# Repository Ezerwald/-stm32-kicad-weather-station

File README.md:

# STM32 KiCad Weather Station

KiCad-based PCB project for an STM32-powered IoT weather station with environmental sensing, real-time clock support, battery charging, and e-paper display connectivity.

> 3D render:

## Overview

This project is a custom two-layer PCB designed in KiCad for a compact embedded weather station.  
The board is built around the **STM32F103C8T6** microcontroller and integrates power management, sensing, display, and timekeeping components into a single design.

The main goal of the project was to practice the complete PCB design workflow: schematic capture, component selection, board layout, and preparation of production files.

## Main features

- STM32F103C8T6 microcontroller
- BME280 environmental sensor
- DS3231S real-time clock
- E-paper display connector
- TP4056 Li-ion battery charging circuit
- AMS1117-3.3 voltage regulator
- USB-C power input
- 5 control buttons
- Status LEDs

## Hardware components

### Core components
- **U1** — STM32F103C8T6
- **U2** — BME280
- **U3** — TP4056
- **U4** — AMS1117-3.3
- **U5** — DS3231S

### Connectors and interfaces
- **P1** — USB_C_Plug
- **J1** — Battery
- **J2** — Prog
- **J3** — E-Paper_Display

### User interface
- **SW1–SW5** — buttons
- **D1** — Blue LED
- **D2** — Green LED
- **D3** — Red LED

## Design files

> Schematic:

> PCB layout:

## Notes

This repository focuses mainly on the PCB design itself rather than firmware implementation.  
The project includes the main design files, screenshots, and fabrication outputs for documentation purposes.

## Tools used

- **KiCad** for schematic and PCB design
- Optional 3D viewer/export from KiCad for board rendering

## Author

**Vladyslav Kyshchun**

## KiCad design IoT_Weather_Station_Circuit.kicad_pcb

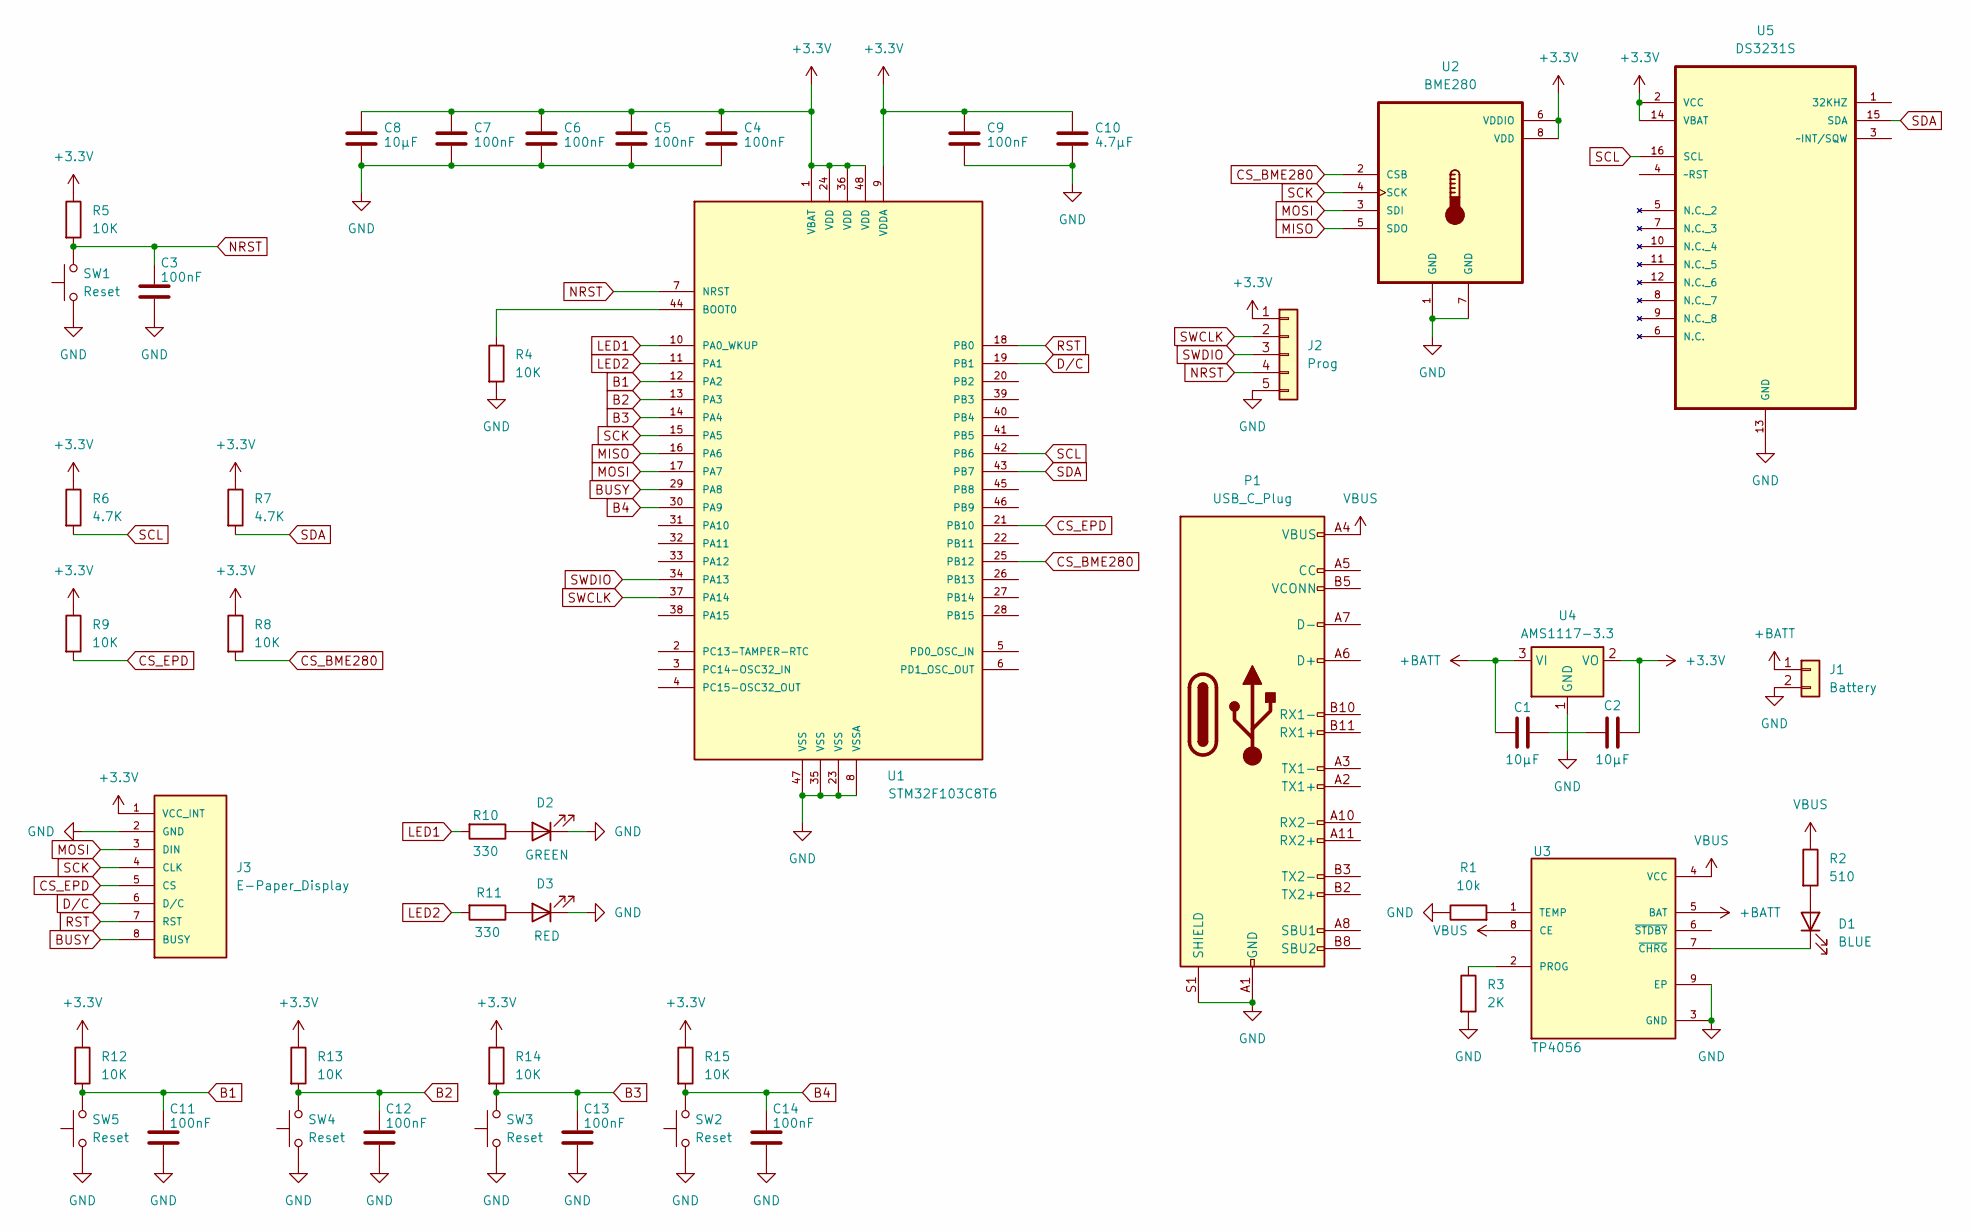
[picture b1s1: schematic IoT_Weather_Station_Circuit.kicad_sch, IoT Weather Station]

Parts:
C1, C2: 10µF; C_0201_0603Metric
C3, C4, C5, C6, C7, C9, C11, C12, C13, C14: 100nF; C_0603_1608Metric
C8: 10µF; C_0603_1608Metric
C10: 4.7µF; C_0603_1608Metric
D1: BLUE; LED_0603_1608Metric
D2: GREEN; D_0201_0603Metric
D3: RED; D_0201_0603Metric
J1: Battery; JST_EH_B2B-EH-A_1x02_P2.50mm_Vertical
J2: Prog; JST_EH_B5B-EH-A_1x05_P2.50mm_Vertical
J3: E-Paper_Display; AMPHENOL_59453-081110ECHLF; PARTREV A
P1: USB_C_Plug; USB_C_Plug_Molex_105444
R1: 10k; R_0603_1608Metric
R2: 510; R_0603_1608Metric
R3: 2K; R_0603_1608Metric
R4, R5, R8, R9, R12, R13, R14, R15: 10K; R_0603_1608Metric
R6, R7: 4.7K; R_0603_1608Metric
R10, R11: 330; R_0603_1608Metric
SW1, SW2, SW3, SW4, SW5: Reset; SW_Push_1P1T_NO_6x6mm_H9.5mm
U1: STM32F103C8T6; STM-32F103C8T6; PARTREV 10
U2: BME280
U3: TP4056
U4: AMS1117-3.3; SOT-223-3_TabPin2
U5: DS3231S; MPN DS3231S#; DigiKey_Part_Number DS3231S#-ND

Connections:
+3.3V: C2.1, C4.1, C5.1, C6.1, C7.1, C8.1, C9.1, C10.1, J2.1, J3.1 (VCC_INT), R5.1, R6.1, R7.1, R8.1, R9.1, R12.1, R13.1, R14.1, R15.1, U1.1 (VBAT), U1.9 (VDDA), U1.24 (VDD), U1.36 (VDD), U1.48 (VDD), U2.6 (VDDIO), U2.8 (VDD), U4.2 (VO), U5.2 (VCC), U5.14 (VBAT)
+BATT: C1.2, J1.1, U3.5 (BAT), U4.3 (VI)
B1: C11.1, R12.2, SW5.2, U1.12 (PA2)
B2: C12.1, R13.2, SW4.2, U1.13 (PA3)
B3: C13.1, R14.2, SW3.2, U1.14 (PA4)
B4: C14.1, R15.2, SW2.2, U1.30 (PA9)
BUSY: J3.8 (BUSY), U1.29 (PA8)
CS_BME280: R8.2, U1.25 (PB12), U2.2 (CSB)
CS_EPD: J3.5 (CS), R9.2, U1.21 (PB10)
D/C: J3.6 (D/C), U1.19 (PB1)
GND: C3.2, C4.2, C5.2, C6.2, C7.2, C8.2, C9.2, C10.2, C11.2, C12.2, C13.2, C14.2, D2.1 (K), D3.1 (K), J1.2, J2.5, J3.2 (GND), P1.A1 (GND), P1.A12 (GND), P1.B1 (GND), P1.B12 (GND), P1.S1 (SHIELD), R1.1, R3.2, R4.2, SW1.1, SW2.1, SW3.1, SW4.1, SW5.1, U1.8 (VSSA), U1.23 (VSS), U1.35 (VSS), U1.47 (VSS), U2.1 (GND), U2.7 (GND), U3.3 (GND), U3.9 (EP), U4.1 (GND), U5.13 (GND)
LED1: R10.2, U1.10 (PA0_WKUP)
LED2: R11.2, U1.11 (PA1)
MISO: U1.16 (PA6), U2.5 (SDO)
MOSI: J3.3 (DIN), U1.17 (PA7), U2.3 (SDI)
NRST: C3.1, J2.4, R5.2, SW1.2, U1.7 (NRST)
unnamed: C1.1, C2.2
unnamed: D1.2 (A), R2.2
unnamed: D1.1 (K), U3.7 (~CHRG)
unnamed: D2.2 (A), R10.1
unnamed: D3.2 (A), R11.1
unnamed: R4.1, U1.44 (BOOT0)
unnamed: R3.1, U3.2 (PROG)
unnamed: R1.2, U3.1 (TEMP)
RST: J3.7 (RST), U1.18 (PB0)
SCK: J3.4 (CLK), U1.15 (PA5), U2.4 (SCK)
SCL: R6.2, U1.42 (PB6), U5.16 (SCL)
SDA: R7.2, U1.43 (PB7), U5.15 (SDA)
SWCLK: J2.2, U1.37 (PA14)
SWDIO: J2.3, U1.34 (PA13)
VBUS: P1.A4 (VBUS), P1.A9 (VBUS), P1.B4 (VBUS), P1.B9 (VBUS), R2.1, U3.4 (VCC), U3.8 (CE)

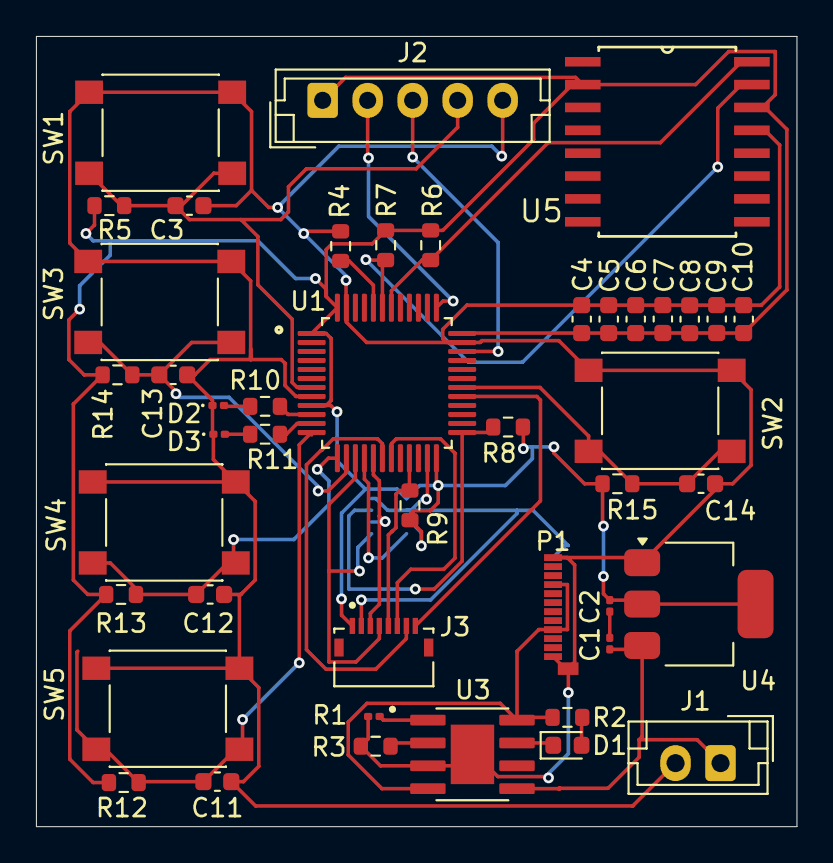
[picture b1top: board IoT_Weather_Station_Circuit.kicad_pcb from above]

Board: 2 copper layers, 42.2 x 43.9 mm, 46 parts (1 on the bottom side), 31 nets.
